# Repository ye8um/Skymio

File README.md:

# Skymio ☁️

## What is Skymio?

Skymio is a small weather display that shows the current temperature, whether it's raining, and the weather forecast for the next three days. It uses an ESP32-C3 and a 2.4-inch LCD screen to show the weather in a simple and easy-to-read way.

## Why I Made It

I wanted to make something that I could actually use every day. Usually, whenever I want to check the weather, I have to open my phone or search it up. So I thought it would be cool to have a small display sitting on my desk that shows the weather automatically.

I also wanted to get more experience designing PCBs and 3D-printed enclosures. I decided to keep the design pretty simple because I wanted it to look clean and not take up too much space.

## How It Works

Skymio uses a Seeed Studio XIAO ESP32-C3, which connects to Wi-Fi and gets weather information from Open-Meteo, a free weather API.

The ESP32 then sends the information to the LCD screen. The display shows the current temperature in Fahrenheit, whether it's raining, and the high and low temperatures for the next three days.

The weather is set to update automatically every 15 minutes, so I don't have to do anything once it's connected.

## Project Images

### PCB Layout

### Schematic

## Components

| Component | Quantity | Purpose |
|---|---:|---|
| [Seeed XIAO ESP32-C3](https://www.seeedstudio.com/Seeed-XIAO-ESP32C3-p-5431.html) | 1 | Controls everything and connects to Wi-Fi |
| [Waveshare 2.4-inch LCD](https://www.waveshare.com/product/2.4inch-lcd-module.htm) | 1 | Displays the weather |
| 10 kΩ resistor | 1 | Pull-up resistor for GPIO8 |
| 10 µF capacitor | 1 | Helps stabilize power |
| 100 nF capacitor | 1 | Helps filter power noise |
| 8-pin male header | 1 | Connects the LCD cable |
| Custom PCB | 1 | Connects all the components |
| USB-C cable | 1 | Powers the ESP32 |
| 3D-printed enclosure | 1 | Holds everything together |
| M2.5 screws and nuts | 4 | Secures the PCB |

## Wiring

| LCD Pin | ESP32-C3 Pin |
|---|---|
| VCC | 3.3V |
| GND | GND |
| DIN | D10 |
| CLK | D8 |
| CS | D3 |
| DC | D4 |
| RST | D5 |
| BL | 3.3V |

## Firmware

I used Arduino to program the ESP32-C3. The code connects to Wi-Fi, requests weather information from Open-Meteo, and displays it on the screen.

The main libraries used are Adafruit GFX, Adafruit ILI9341, and ArduinoJson. I also used the ESP32 WiFi and HTTPClient libraries to get weather information.

To use the code, open `skymio.ino` in Arduino IDE, install the required libraries, and enter your Wi-Fi information and location coordinates. After uploading it to the ESP32-C3, the display should start showing the weather once it connects to Wi-Fi.

## PCB and Enclosure

I designed the schematic and PCB in KiCad. Since the project only needs an ESP32-C3 and an LCD, the circuit is pretty simple. I added two capacitors for power filtering and a resistor for one of the ESP32's pins.

For the enclosure, I used Fusion 360. I wanted the screen to sit flush with the front so the whole device would look neat and minimalistic.

The LCD is mounted separately from the main PCB and connects using an 8-pin cable. The PCB sits behind the screen and is held in place using screws. I also placed the USB-C port on the side so the device can be powered without opening the case.

## Challenges

One of the things I had to figure out was how to connect the LCD to my custom PCB. At first, I planned to use a JST connector, but I realized I could use an 8-pin male header with the female jumper wires instead.

I also spent time figuring out how to position everything inside the enclosure. I wanted the screen to sit flush while keeping the edges as small as possible. This meant I had to account for the screen's dimensions, PCB size, mounting holes, and enough space for the wires.

## Resources

Here are some of the resources I used or referenced while working on Skymio.

- [Seeed XIAO ESP32-C3 Documentation](https://wiki.seeedstudio.com/XIAO_ESP32C3_Getting_Started/)
- [Waveshare LCD Documentation](https://www.waveshare.com/wiki/2.4inch_LCD_Module)
- [Adafruit ILI9341 Library](https://github.com/adafruit/Adafruit_ILI9341)
- [Adafruit GFX Library](https://github.com/adafruit/Adafruit-GFX-Library)
- [Open-Meteo Weather API](https://open-meteo.com/en/docs)
- [ArduinoJson Documentation](https://arduinojson.org/)

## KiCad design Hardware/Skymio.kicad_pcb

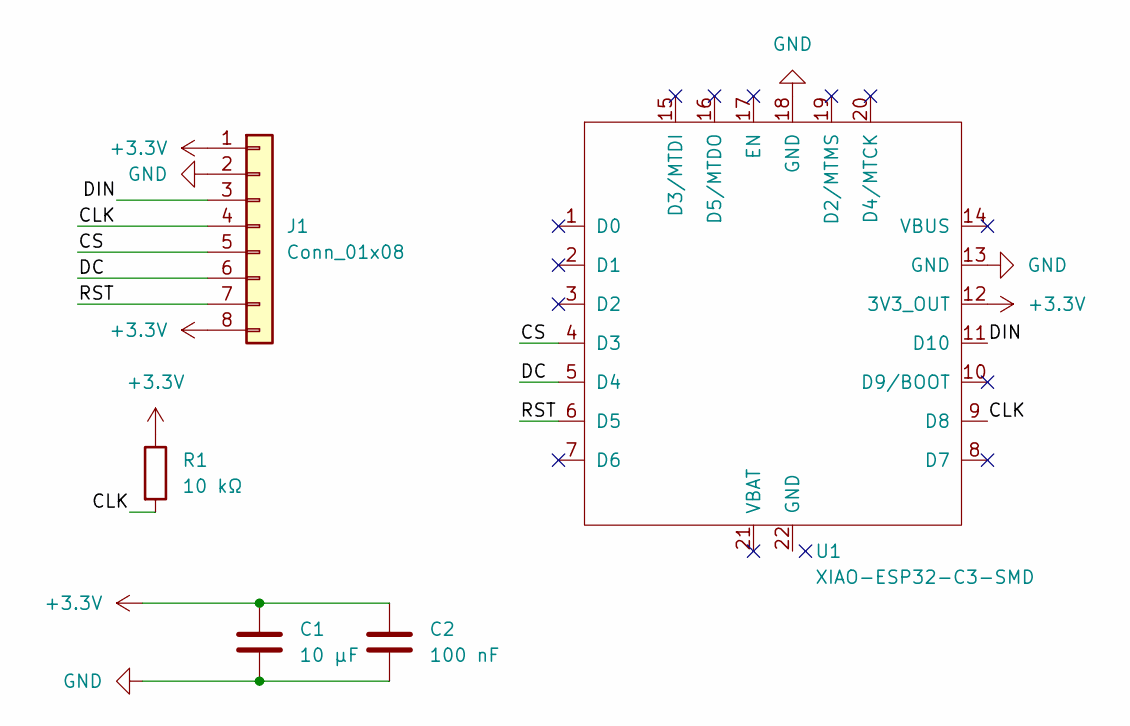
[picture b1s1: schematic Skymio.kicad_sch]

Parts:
C1: 10 µF; C_0805_2012Metric
C2: 100 nF; C_0805_2012Metric
J1: Conn_01x08; PinHeader_1x08_P2.54mm_Vertical
R1: 10 kΩ; R_0805_2012Metric
U1: XIAO-ESP32-C3-SMD; XIAO-ESP32-S3-SMD

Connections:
+3.3V: C1.1, C2.1, J1.1, J1.8, R1.1, U1.12 (3V3_OUT)
/CLK: J1.4, R1.2, U1.9 (D8)
/CS: J1.5, U1.4 (D3)
/DC: J1.6, U1.5 (D4)
/DIN: J1.3, U1.11 (D10)
/RST: J1.7, U1.6 (D5)
GND: C1.2, C2.2, J1.2, U1.13 (GND), U1.18 (GND)

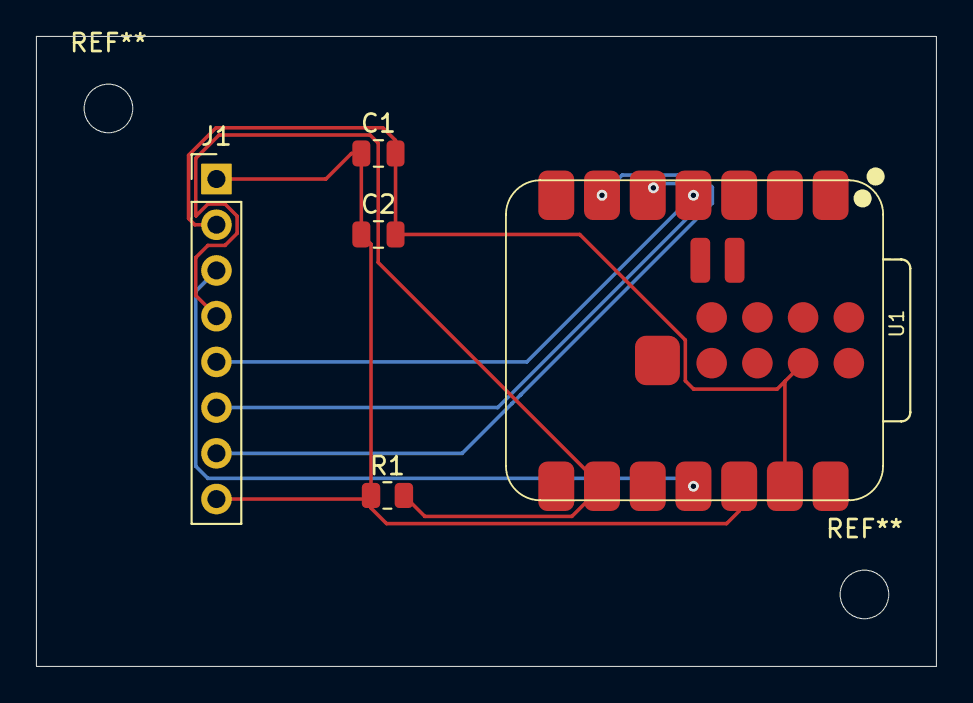
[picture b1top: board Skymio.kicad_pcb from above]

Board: 2 copper layers, 50.0 x 35.0 mm, 5 parts (0 on the bottom side), 7 nets.
